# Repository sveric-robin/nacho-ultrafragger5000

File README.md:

# NACHO ULTRAFRAGGER 5000

### THE ULTIMATE THROUGH-HOLE MECHANICAL GAMING TKL KEYBOARD. ACTIVE COOLING NOT INCLUDED. ACTIVE GAMING VERY MUCH INCLUDED.

You thought your off-the-shelf keyboard was good enough? You thought wrong. The **Nacho UltraFragger 5000** is a no-compromise, hand-solderable, through-hole-only tenkeyless mechanical keyboard engineered from the ground up for those who demand MAXIMUM PERFORMANCE and ZERO SMD components. Every resistor, every diode, every capacitor — all glorious through-hole, all day long.

Featuring a built-in **USB hub** and a **volume slider** because real fraggers don't alt-tab to change the volume. They twist a knob. Mid-firefight. Without blinking.

## Features

- **100% Through-Hole Construction** — If you can't see the solder joint with your naked eye, we don't want it
- **TKL Layout** — Full-size is for spreadsheets. TKL is for warriors
- **USB Type-C** — Because it's not 2012
- **Integrated USB Hub** — Plug in your mouse, your headset, your backup mouse, whatever
- **Hardware Volume Slider** — Analog control for analog legends
- **ATmega32A Powered** — The reliable workhorse that runs QMK like a champ
- **Fully Open Source** — Schematics, PCB, case files — it's all here, do what you want with it

## Origins

This project is loosely based on the legendary [Mysterium keyboard](https://github.com/coseyfannitutti/mysterium) by coseyfannitutti — the board that proved you don't need a factory to build a world-class keyboard. We took that foundation, cranked every dial to 11, strapped a USB hub and a volume slider to it, and named it something truly worthy of its power.

## Status

Under active development. Things will break. Things will be re-routed. Capacitors may be added and removed on a whim. This is the way.

## License

See [LICENSE](./LICENSE) for details.

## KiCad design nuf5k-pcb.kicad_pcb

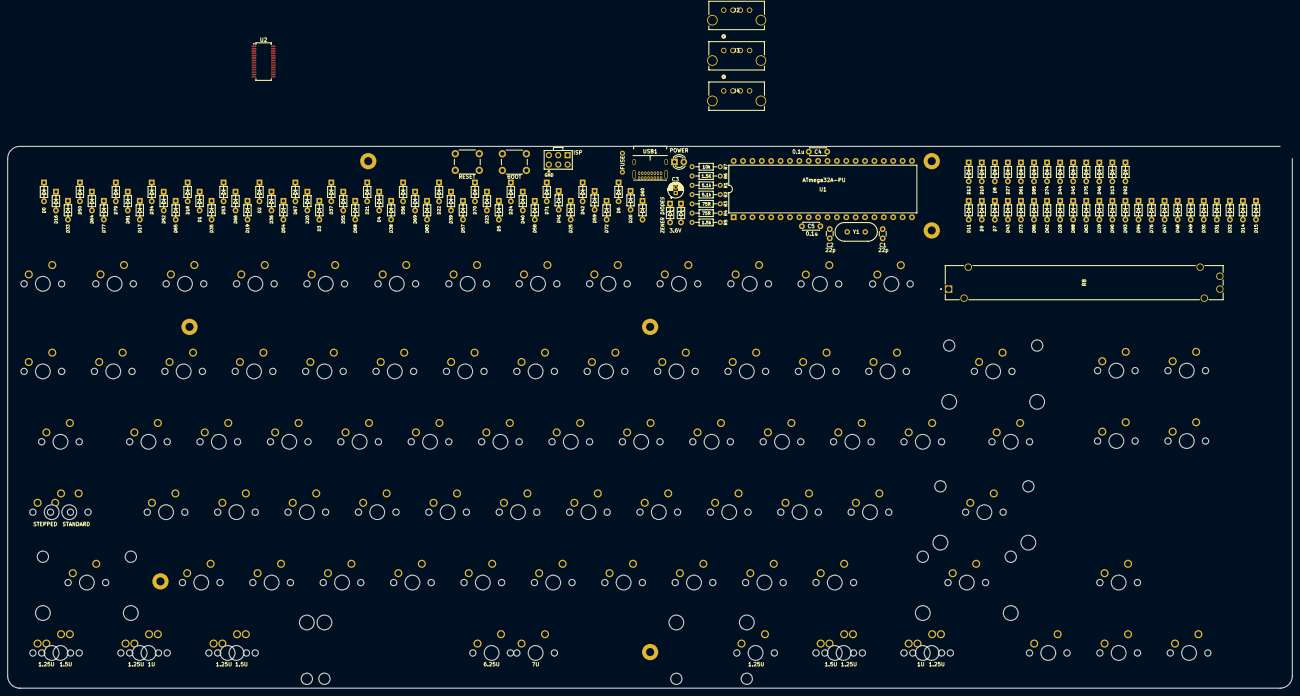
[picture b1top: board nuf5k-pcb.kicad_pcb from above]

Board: 2 copper layers, 347.7 x 146.6 mm, 204 parts (0 on the bottom side), 122 nets, no tracks yet.

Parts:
BOOT1: BOOT; SW_PUSH_6mm
C1, C2: 22p; C_Disc_D3.0mm_W1.6mm_P2.50mm
C3: 4.7u; CP_Radial_D4.0mm_P1.50mm
C4, C5: 0.1u; C_Disc_D4.3mm_W1.9mm_P5.00mm
D0, D1, D2, D3, D4, D5, D6, D7, D8, D9, D10, D11, D12, D13, D14, D15, D16, D17, D18, D19, D20, D21, D22, D23, D24, D25, D26, D27, D28, D29, D30, D31, D32, D33, D34, D35, D36, D37, D38, D39, D40, D41, D42, D43, D44, D45, D46, D47, D48, D49, D50, D52, D53, D54, D55, D56, D57, D58, D59, D60, D61, D62, D63, D64, D65, D66, D67, D68, D69, D70, D71, D72, D73, D74, D75, D76, D77, D79, D81, D83, D85, D86, D88, D90, D92, D93, D94: D_Small; D_DO-35_SOD27_P5.08mm_Horizontal
D95, D96: 3.6V; D_DO-35_SOD27_P5.08mm_Horizontal
F1: 500mA; polyfuse_5.1mm
J1: AVR-ISP-6; AVR_ICSP_3x2
J2, J3, J4: 1734366-1; CONN4_1734366-1_TEC
LED1: POWER; LED_D3.0mm
R1, R2: 5.1k; R_Axial_DIN0204_L3.6mm_D1.6mm_P7.62mm_Horizontal
R3, R4: 75R; R_Axial_DIN0204_L3.6mm_D1.6mm_P7.62mm_Horizontal
R5: 1.5k; R_Axial_DIN0204_L3.6mm_D1.6mm_P7.62mm_Horizontal
R6: 1.5K; R_Axial_DIN0204_L3.6mm_D1.6mm_P7.62mm_Horizontal
R7: 10k; R_Axial_DIN0204_L3.6mm_D1.6mm_P7.62mm_Horizontal
R8: PTA6043-2015DPB103; POT_PTA6043
RESET1: RESET; SW_PUSH_6mm
ST83: 6.25U; MX-6.25U-Stabilizer
ST84: 7U; MX-7U-Stabilizer
SW0, SW1, SW2, SW3, SW4, SW5, SW6, SW7, SW8, SW9, SW10, SW11, SW12, SW16, SW17, SW18, SW19, SW20, SW21, SW22, SW23, SW24, SW25, SW26, SW27, SW28, SW30, SW31, SW34, SW35, SW36, SW37, SW38, SW39, SW40, SW41, SW42, SW43, SW44, SW45, SW47, SW48, SW52, SW53, SW54, SW55, SW56, SW57, SW58, SW59, SW60, SW61, SW62, SW65, SW66, SW67, SW68, SW69, SW70, SW71, SW72, SW73, SW74, SW76, SW80, SW83, SW84, SW89, SW92, SW93, SW94: KEYSW; SW_Cherry_MX1A_1.00u_PCB-NOSCREEN
SW29: KEYSW; SW_Cherry_MX1A_2.00u_PCBNOSCREEN
SW33, SW46, SW77, SW81, SW86: KEYSW; SW_Cherry_MX1A_1.50u_PCBNOSCREEN
SW50: KEYSW; SW_Cherry_MX1A_1.75u_PCBNOSCREEN
SW51, SW78, SW79, SW82, SW85, SW87, SW88: KEYSW; SW_Cherry_MX1A_1.25u_PCBNOSCREEN
SW63, SW64: KEYSW; SW_Cherry_MX1A_2.25u_PCBNOSCREEN
SW75: KEYSW; SW_Cherry_MX1A_2.75u_PCB_NOSCREEN
U1: ATmega32A-PU; DIP-40_W15.24mm
U2: FE1.1s; SSOP-28_3.9x9.9mm_P0.635mm
USB1: USB_C_GCT_USB4085
Y1: Crystal; Crystal_HC49-4H_Vertical

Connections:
+5V: C3.1, C4.1, C5.1, F1.1, J1.2 (VCC), LED1.2 (A), R5.1, R7.1, U1.10 (VCC), U1.30 (AVCC)
D+: R4.1, U1.16 (PD2)
D-: R3.1, U1.17 (PD3)
GND: BOOT1.1, C1.2, C2.2, C3.2, C4.2, C5.2, D95.2 (A), D96.2 (A), J1.6 (GND), R1.1, R2.2, R6.2, RESET1.1, U1.11 (GND), U1.31 (GND), USB1.A1 (GND), USB1.A12 (GND), USB1.B1 (GND), USB1.B12 (GND), USB1.S1 (SHIELD)
MISO: J1.1 (MISO), U1.7 (PB6)
MOSI: J1.4 (MOSI), U1.6 (PB5)
unnamed: D0.2 (A), SW0.2
unnamed: D1.2 (A), SW1.2
unnamed: D2.2 (A), SW2.2
unnamed: D3.2 (A), SW3.2
unnamed: D4.2 (A), SW4.2
unnamed: D5.2 (A), SW5.2
unnamed: D6.2 (A), SW6.2
unnamed: D7.2 (A), SW7.2
unnamed: D8.2 (A), SW8.2
unnamed: D9.2 (A), SW9.2
unnamed: D10.2 (A), SW10.2
unnamed: D11.2 (A), SW11.2
unnamed: D12.2 (A), SW12.2
unnamed: D16.2 (A), SW16.2
unnamed: D17.2 (A), SW17.2
unnamed: D18.2 (A), SW18.2
unnamed: D19.2 (A), SW19.2
unnamed: D20.2 (A), SW20.2
unnamed: D21.2 (A), SW21.2
unnamed: D22.2 (A), SW22.2
unnamed: D23.2 (A), SW23.2
unnamed: D24.2 (A), SW24.2
unnamed: D25.2 (A), SW25.2
unnamed: D26.2 (A), SW26.2
unnamed: D27.2 (A), SW27.2
unnamed: D28.2 (A), SW28.2
unnamed: D29.2 (A), SW29.2
unnamed: D30.2 (A), SW30.2
unnamed: D31.2 (A), SW31.2
unnamed: D33.2 (A), SW33.2
unnamed: D34.2 (A), SW34.2
unnamed: D35.2 (A), SW35.2
unnamed: D36.2 (A), SW36.2
unnamed: D37.2 (A), SW37.2
unnamed: D38.2 (A), SW38.2
unnamed: D39.2 (A), SW39.2
unnamed: D40.2 (A), SW40.2
unnamed: D41.2 (A), SW41.2
unnamed: D42.2 (A), SW42.2
unnamed: D43.2 (A), SW43.2
unnamed: D44.2 (A), SW44.2
unnamed: D45.2 (A), SW45.2
unnamed: D46.2 (A), SW46.2
unnamed: D47.2 (A), SW47.2
unnamed: D48.2 (A), SW48.2
unnamed: D50.2 (A), SW50.2, SW51.2
unnamed: D52.2 (A), SW52.2
unnamed: D53.2 (A), SW53.2
unnamed: D54.2 (A), SW54.2
unnamed: D55.2 (A), SW55.2
unnamed: D56.2 (A), SW56.2
unnamed: D57.2 (A), SW57.2
unnamed: D58.2 (A), SW58.2
unnamed: D59.2 (A), SW59.2
unnamed: D60.2 (A), SW60.2
unnamed: D61.2 (A), SW61.2
unnamed: D62.2 (A), SW62.2
unnamed: D63.2 (A), SW63.2
unnamed: D64.2 (A), SW64.2
unnamed: D65.2 (A), SW65.2
unnamed: D66.2 (A), SW66.2
unnamed: D67.2 (A), SW67.2
unnamed: D68.2 (A), SW68.2
unnamed: D69.2 (A), SW69.2
unnamed: D70.2 (A), SW70.2
unnamed: D71.2 (A), SW71.2
unnamed: D72.2 (A), SW72.2
unnamed: D73.2 (A), SW73.2
unnamed: D74.2 (A), SW74.2
unnamed: D75.2 (A), SW75.2
unnamed: D76.2 (A), SW76.2
unnamed: D77.2 (A), SW77.2, SW78.2
unnamed: D79.2 (A), SW79.2, SW80.2
unnamed: D81.2 (A), SW81.2, SW82.2
unnamed: D83.2 (A), SW83.2, SW84.2
unnamed: D85.2 (A), SW85.2
unnamed: D86.2 (A), SW86.2, SW87.2
unnamed: D88.2 (A), SW88.2, SW89.2
unnamed: D92.2 (A), SW92.2
unnamed: D93.2 (A), SW93.2
unnamed: D94.2 (A), SW94.2
unnamed: D95.1 (K), R3.2, R5.2, USB1.A7 (DN1), USB1.B7 (DN2)
unnamed: D96.1 (K), R4.2, USB1.A6 (DP1), USB1.B6 (DP2)
unnamed: LED1.1 (K), R6.1
unnamed: C1.1, U1.13 (XTAL1), Y1.1
unnamed: C2.1, U1.12 (XTAL2), Y1.2
unnamed: R1.2, USB1.A5 (CC1)
unnamed: R2.1, USB1.B5 (CC2)
SCK: J1.3 (SCK), U1.8 (PB7)
VCC: F1.2, USB1.A4 (VBUS), USB1.A9 (VBUS), USB1.B4 (VBUS), USB1.B9 (VBUS)
boot: BOOT1.2, U1.18 (PD4)
col0: SW0.1, SW16.1, SW33.1, SW50.1, SW51.1, SW64.1, SW77.1, SW78.1, U1.40 (PA0)
col1: SW17.1, SW34.1, SW52.1, SW65.1, SW79.1, SW80.1, U1.1 (PB0)
col2: SW1.1, SW18.1, SW35.1, SW53.1, SW66.1, SW81.1, SW82.1, U1.39 (PA1)
col3: SW2.1, SW19.1, SW36.1, SW54.1, SW67.1, U1.2 (PB1)
col4: SW3.1, SW20.1, SW37.1, SW55.1, SW68.1, U1.38 (PA2)
col5: SW4.1, SW21.1, SW38.1, SW56.1, SW69.1, U1.3 (PB2)
col6: SW5.1, SW22.1, SW39.1, SW57.1, SW70.1, SW83.1, SW84.1, U1.37 (PA3)
col7: SW6.1, SW23.1, SW40.1, SW58.1, SW71.1, U1.4 (PB3)
col8: SW7.1, SW24.1, SW41.1, SW59.1, SW72.1, U1.36 (PA4)
col9: SW8.1, SW25.1, SW42.1, SW60.1, SW73.1, SW85.1, U1.5 (PB4)
col10: SW26.1, SW43.1, SW61.1, SW74.1, SW86.1, SW87.1, U1.35 (PA5)
col11: SW9.1, SW27.1, SW44.1, SW62.1, U1.34 (PA6)
col12: SW10.1, SW28.1, SW45.1, SW88.1, SW89.1, U1.33 (PA7)
col13: SW11.1, SW29.1, SW46.1, SW63.1, SW75.1, U1.20 (PD6)
col14: SW12.1, U1.19 (PD5)
col15: SW30.1, SW47.1, SW92.1, U1.15 (PD1)
col16: SW31.1, SW48.1, SW76.1, SW93.1, U1.14 (PD0)
col17: SW94.1, U1.21 (PD7)
reset: J1.5 (~RST), R7.2, RESET1.2, U1.9 (~RESET)
row0: D0.1 (K), D1.1 (K), D2.1 (K), D3.1 (K), D4.1 (K), D5.1 (K), D6.1 (K), D7.1 (K), D8.1 (K), D9.1 (K), D10.1 (K), D11.1 (K), D12.1 (K), D13.1 (K), D14.1 (K), D15.1 (K), U1.24 (PC2)
row1: D16.1 (K), D17.1 (K), D18.1 (K), D19.1 (K), D20.1 (K), D21.1 (K), D22.1 (K), D23.1 (K), D24.1 (K), D25.1 (K), D26.1 (K), D27.1 (K), D28.1 (K), D29.1 (K), D30.1 (K), D31.1 (K), D32.1 (K), U1.25 (PC3)
row2: D33.1 (K), D34.1 (K), D35.1 (K), D36.1 (K), D37.1 (K), D38.1 (K), D39.1 (K), D40.1 (K), D41.1 (K), D42.1 (K), D43.1 (K), D44.1 (K), D45.1 (K), D46.1 (K), D47.1 (K), D48.1 (K), D49.1 (K), U1.29 (PC7)
row3: D50.1 (K), D52.1 (K), D53.1 (K), D54.1 (K), D55.1 (K), D56.1 (K), D57.1 (K), D58.1 (K), D59.1 (K), D60.1 (K), D61.1 (K), D62.1 (K), D63.1 (K), U1.26 (PC4)
row4: D64.1 (K), D65.1 (K), D66.1 (K), D67.1 (K), D68.1 (K), D69.1 (K), D70.1 (K), D71.1 (K), D72.1 (K), D73.1 (K), D74.1 (K), D75.1 (K), D76.1 (K), U1.28 (PC6)
row5: D77.1 (K), D79.1 (K), D81.1 (K), D83.1 (K), D85.1 (K), D86.1 (K), D88.1 (K), D90.1 (K), D92.1 (K), D93.1 (K), D94.1 (K), U1.27 (PC5)

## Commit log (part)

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2026-02-13 Initial commit: fork from coseyfannitutti/mysterium as nacho-ultrafragger5000
2026-02-14 added some usb stuff
2026-03-06 added volume button
